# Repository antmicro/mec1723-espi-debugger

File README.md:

# MEC1723 eSPI Debugger

Copyright (c) 2026 [Antmicro](https://www.antmicro.com)

## Overview

This project contains open hardware design files for a debug board based on Microchip MEC1723 embedded controller which includes ARM Cortex-M4 core and eSPI physical interface.
The board is designed to aid development, bring-up and integration of eSPI-based data link between servers (HPMs) and Data Center Secure Control Modules (DC-SCMs).
The board has a 0.1 inch pin header connector which allows to connect it to the eSPI bus in the system under development.
The board provides USB-accessible UART and JTAG interfaces, Port 80 status display and local flash storage for the MEC1723 firmware.
MEC1723 controllers are supported in [Zephyr](https://www.zephyrproject.org/) RTOS

The PCB design files were prepared in KiCad 10.x.

## Key features

* Microchip [MEC1723](https://www.microchip.com/en-us/product/mec1723) embedded controller with ARM Cortex-M4 and eSPI interface
* Generic 0.1 inch pinhead connector
* USB-C port with FTDI FT2232H USB interface bridge
* UART and JTAG interfaces accessible from the USB interface bridge
* 1 Gb QSPI NOR Flash for MEC1723 firmware storage
* Port 80 (POST code) display with dual seven-segment LED indicator
* Tag-Connect headers for debug and programming access
* 62 x 87 mm (2.44 x 3.42 inch) PCB outline

## Project structure

The main directory contains KiCad PCB project files, the LICENSE, and this README, and the img directory contains graphics for this README.

## License

This project is licensed under the [Apache-2.0](LICENSE) license.

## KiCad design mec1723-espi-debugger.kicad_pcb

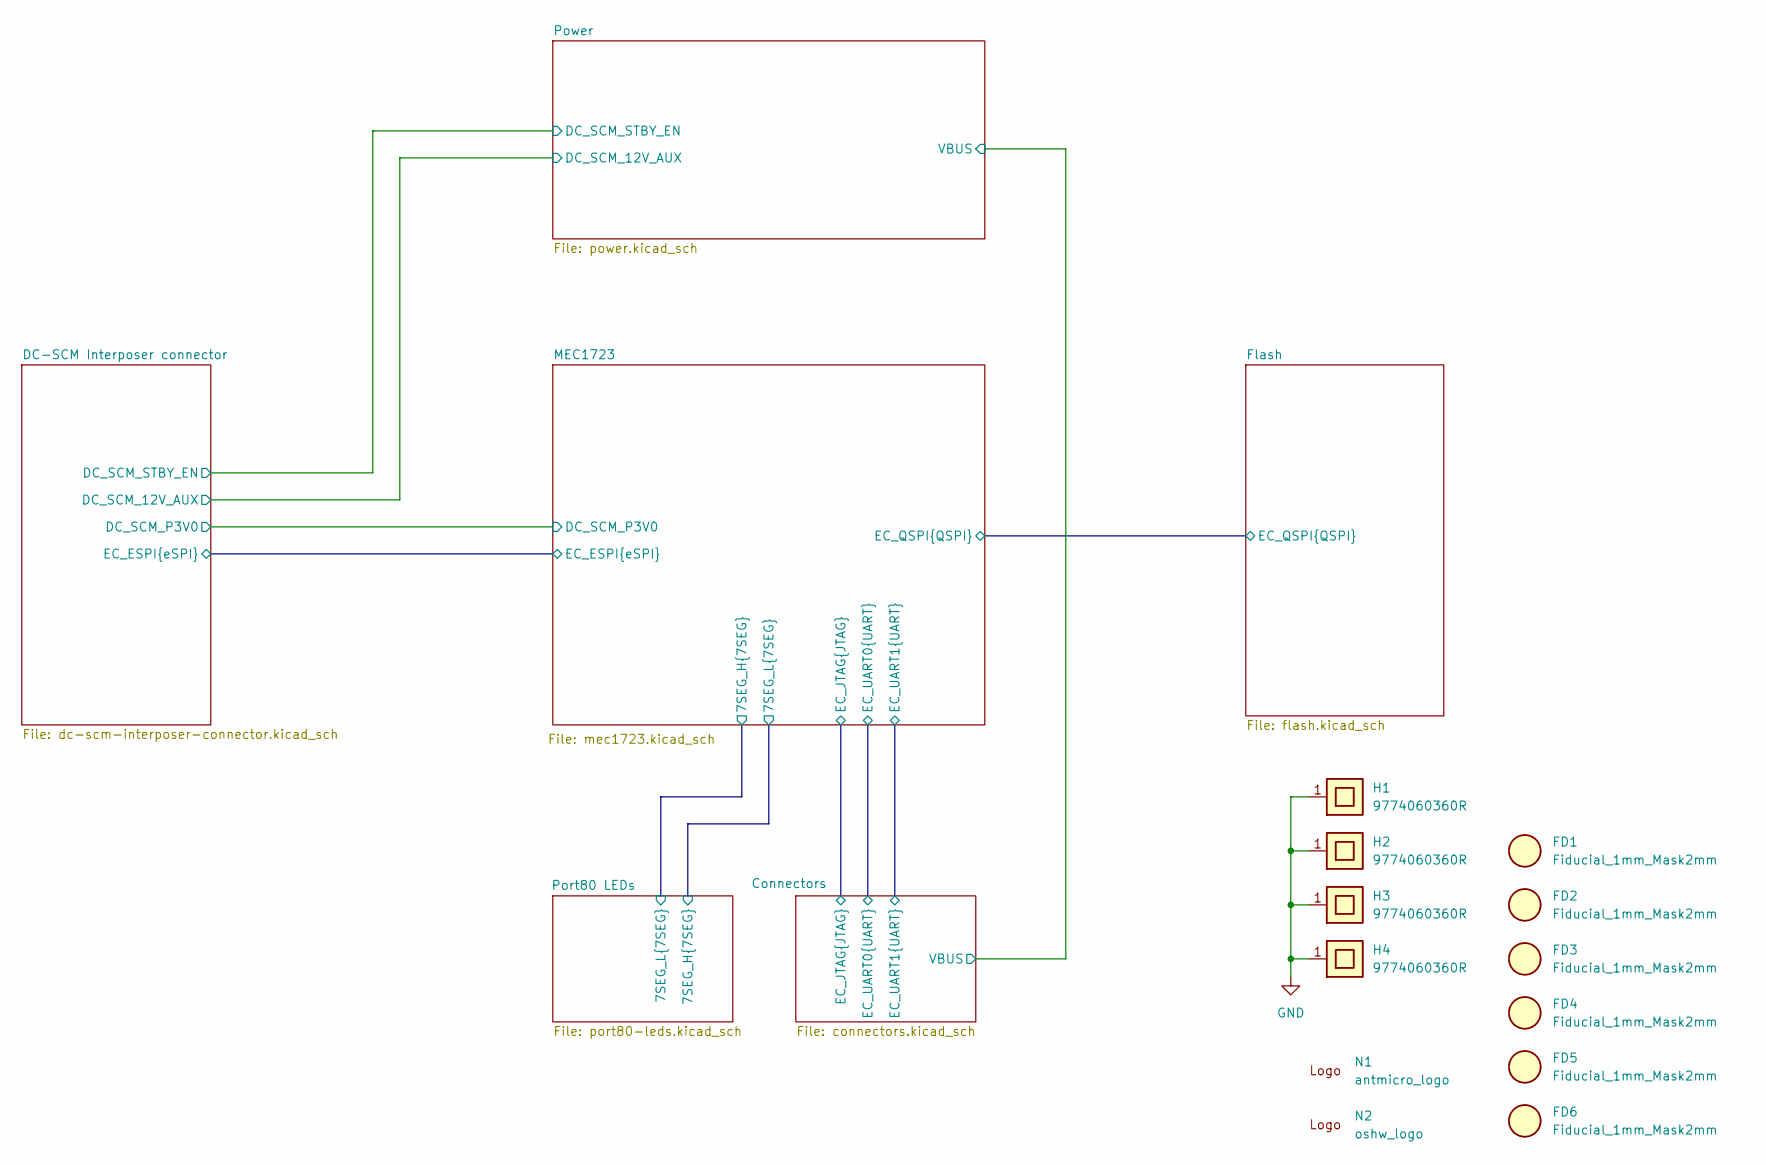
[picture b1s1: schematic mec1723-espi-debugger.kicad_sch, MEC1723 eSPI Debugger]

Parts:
FD1, FD2, FD3, FD4, FD5, FD6: Fiducial_1mm_Mask2mm
H1, H2, H3, H4: Spacer_Drill4.4mm_H6mm_9774060360R; MPN 9774060360R
N1: antmicro_logo; antmicro-logo_scaled_12mm
N2: oshw_logo; oshw-logo

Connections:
GND: H1.1, H2.1, H3.1, H4.1; also elsewhere on the board

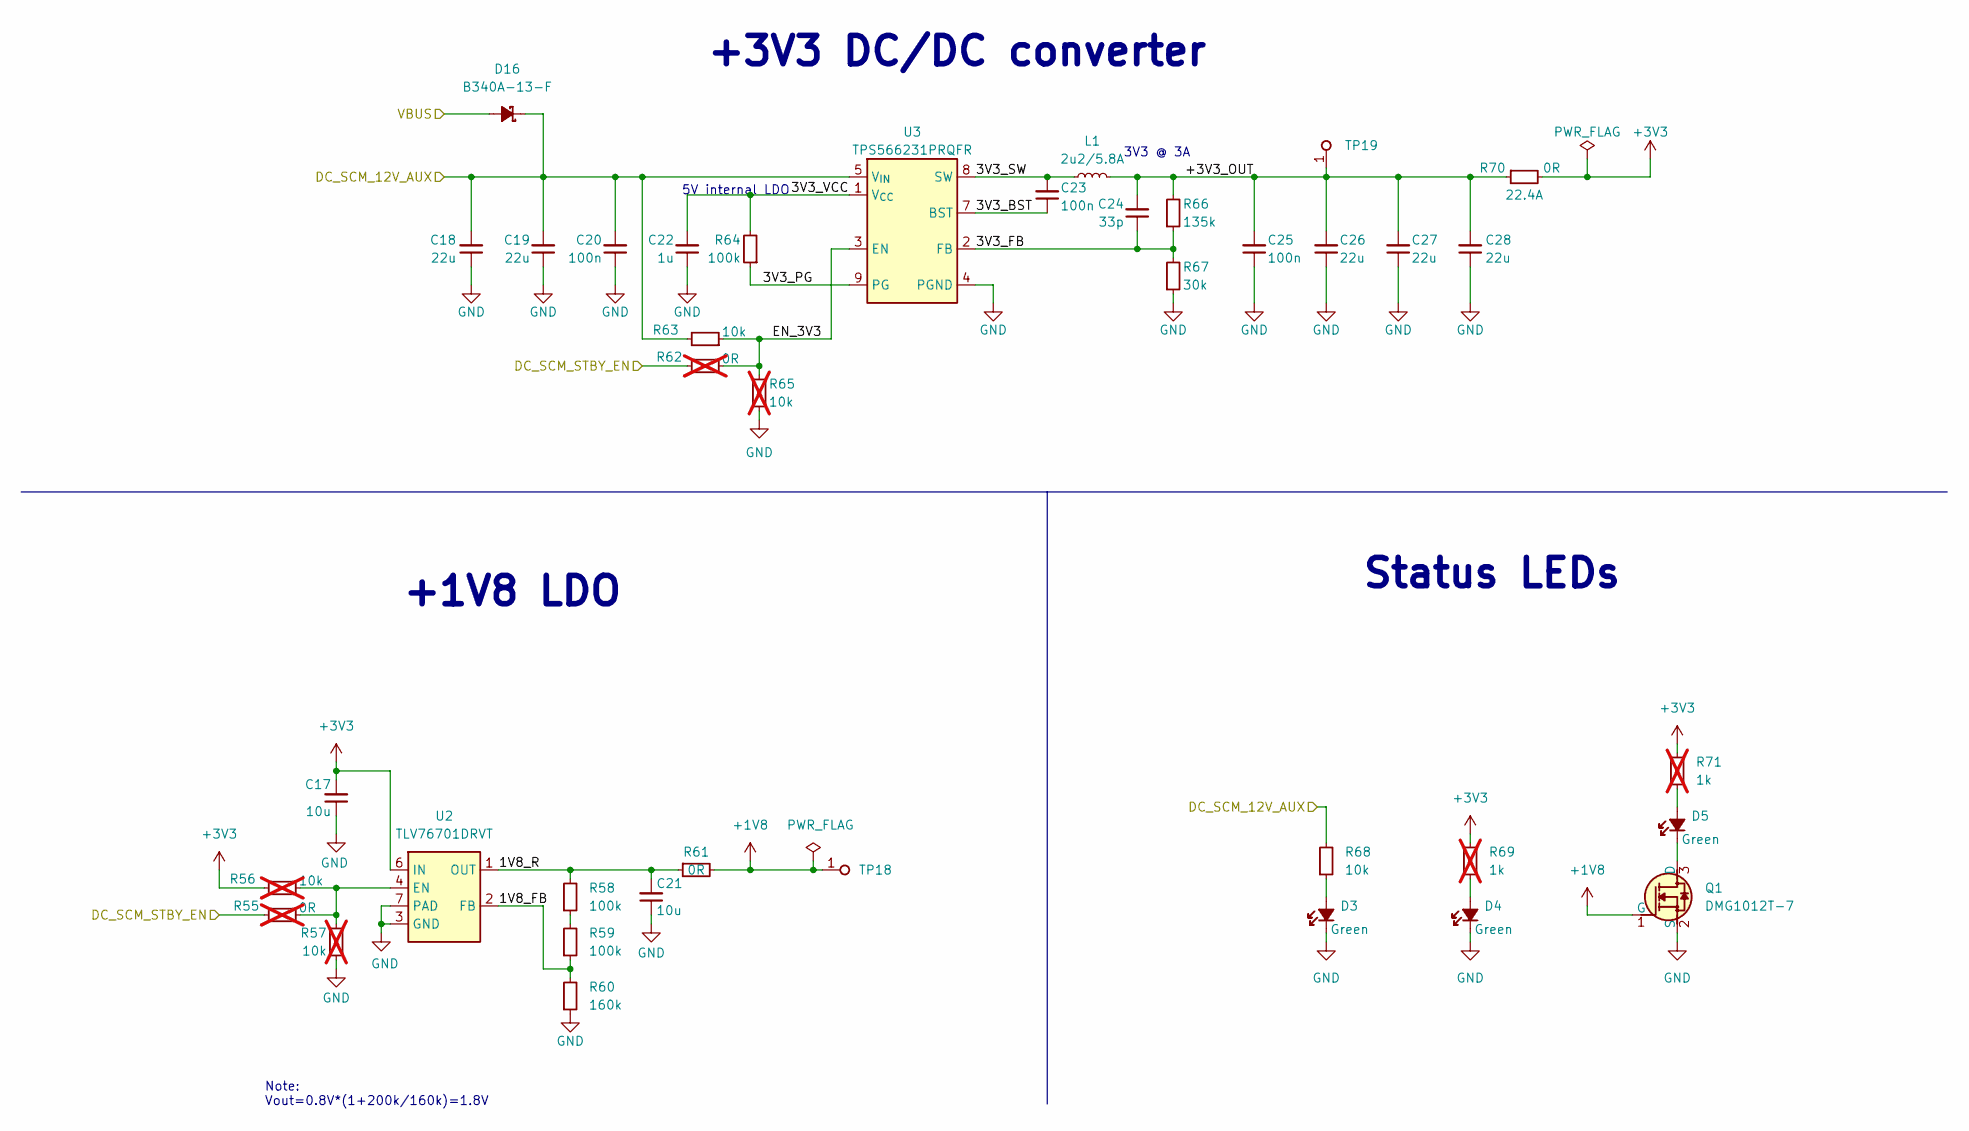
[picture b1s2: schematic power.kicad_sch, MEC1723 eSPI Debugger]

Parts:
C17, C21: C_10u_10V_0402; C_0402_1005Metric; Voltage 10V; MPN GRM155R61A106ME11D
C18, C19, C26, C27, C28: C_22u_16V_0603; C_0603_1608Metric_EIA; Voltage 16V; MPN CL10A226MO7JZNC
C20, C23, C25: C_100n_0402; C_0402_1005Metric; Voltage 50V; MPN GRM155R61H104KE14D
C22: C_1u_25V_0402; C_0402_1005Metric; Voltage 25V; MPN GRM155R61E105KE11J
C24: C_33p_0402; C_0402_1005Metric; MPN 04025A330FAT2A
D3, D4, D5: LED_G_0603_LTST-C190GKT; LED_0603_1608Metric_G; MPN LTST-C190GKT
D16: B340A-13-F; D_SMA; MPN B340A-13-F
L1: L_2u2_5.8A_WE-PMFI-35329222; L_WE-PMFI-353220; MPN 74479335329222
Q1: DMG1012T-7; SOT-523; MPN DMG1012T-7
R55, R62: R_0R_0402; R_0402_1005Metric; MPN ERJ2GE0R00X; not fitted
R56, R57, R65: R_10k_0402; R_0402_1005Metric; Tolerance 1%; MPN CR0402-FX-1002GLF; not fitted
R58, R59, R64: R_100k_0402; R_0402_1005Metric; Tolerance 1%; MPN CR0402-FX-1003GLF
R60: R_160k_0402; R_0402_1005Metric; Tolerance 1%; MPN CR0402-FX-1603GLF
R61: R_0R_0402; R_0402_1005Metric; MPN ERJ2GE0R00X
R63, R68: R_10k_0402; R_0402_1005Metric; Tolerance 1%; MPN CR0402-FX-1002GLF
R66: R_135k_0402; R_0402_1005Metric; Tolerance 0.1%; MPN RT0805BRD07135KL
R67: R_30k_0402; R_0402_1005Metric; Tolerance 1%; MPN CR0402-FX-3002GLF
R69, R71: R_1k_0402; R_0402_1005Metric; Tolerance 1%; MPN CR0402-FX-1001GLF; not fitted
R70: R_0R_22.4A_0603; R_0603_1608Metric; Tolerance template_tolerance; MPN PMR03EZPJ000
TP18, TP19: TP_0.75mm_SMD; TP_SMD_0.75mm
U2: TLV76701_WSON; WSON-6-1EP_2x2mm_P0.65mm; MPN TLV76701DRVT
U3: TPS566231P; VQFN-HR-9_2x1.5mm; MPN TPS566231PRQFR

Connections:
+1V8: Q1.1 (G), R61.2, TP18.1 (1_1); also elsewhere on the board
+3V3: C17.2, R56.2, R69.2, R70.2, R71.2, U2.6 (IN); also elsewhere on the board
/Connectors/VBUS: D16.2 (A); also elsewhere on the board
/DC-SCM Interposer connector/DC_SCM_12V_AUX: C18.2, C19.2, C20.2, D16.1 (C), R63.2, R68.2, U3.5 (V_{IN}), U3.6 (V_{IN}); also elsewhere on the board
/DC-SCM Interposer connector/DC_SCM_STBY_EN: R55.1, R62.1; also elsewhere on the board
/Power/1V8_FB: R59.1, R60.2, U2.2 (FB)
/Power/1V8_R: C21.2, R58.2, R61.1, U2.1 (OUT)
/Power/3V3_BST: C23.1, U3.7 (BST)
/Power/3V3_FB: C24.1, R66.1, R67.2, U3.2 (FB)
/Power/3V3_PG: R64.1, U3.9 (PG)
/Power/3V3_SW: C23.2, L1.1, U3.8 (SW)
/Power/3V3_VCC: C22.2, R64.2, U3.1 (V_{CC})
/Power/+3V3_OUT: C24.2, C25.2, C26.2, C27.2, C28.2, L1.2, R66.2, R70.1, TP19.1 (1_1)
/Power/EN_3V3: R62.2, R63.1, R65.2, U3.3 (EN)
GND: C17.1, C18.1, C19.1, C20.1, C21.1, C22.1, C25.1, C26.1, C27.1, C28.1, D3.1 (C), D4.1 (C), Q1.2 (S), R57.1, R60.1, R65.1, R67.1, U2.3 (GND), U2.5 (GND), U2.7 (PAD), U3.4 (PGND); also elsewhere on the board
unnamed: D3.2 (A), R68.1
unnamed: D4.2 (A), R69.1
unnamed: D5.2 (A), R71.1
unnamed: D5.1 (C), Q1.3 (D)
unnamed: R58.1, R59.2
unnamed: R55.2, R56.1, R57.2, U2.4 (EN)

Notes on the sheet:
Note: Vout=0.8V*(1+200k/160k)=1.8V
Status LEDs
+1V8 LDO
3V3 @ 3A
5V internal LDO
+3V3 DC/DC converter

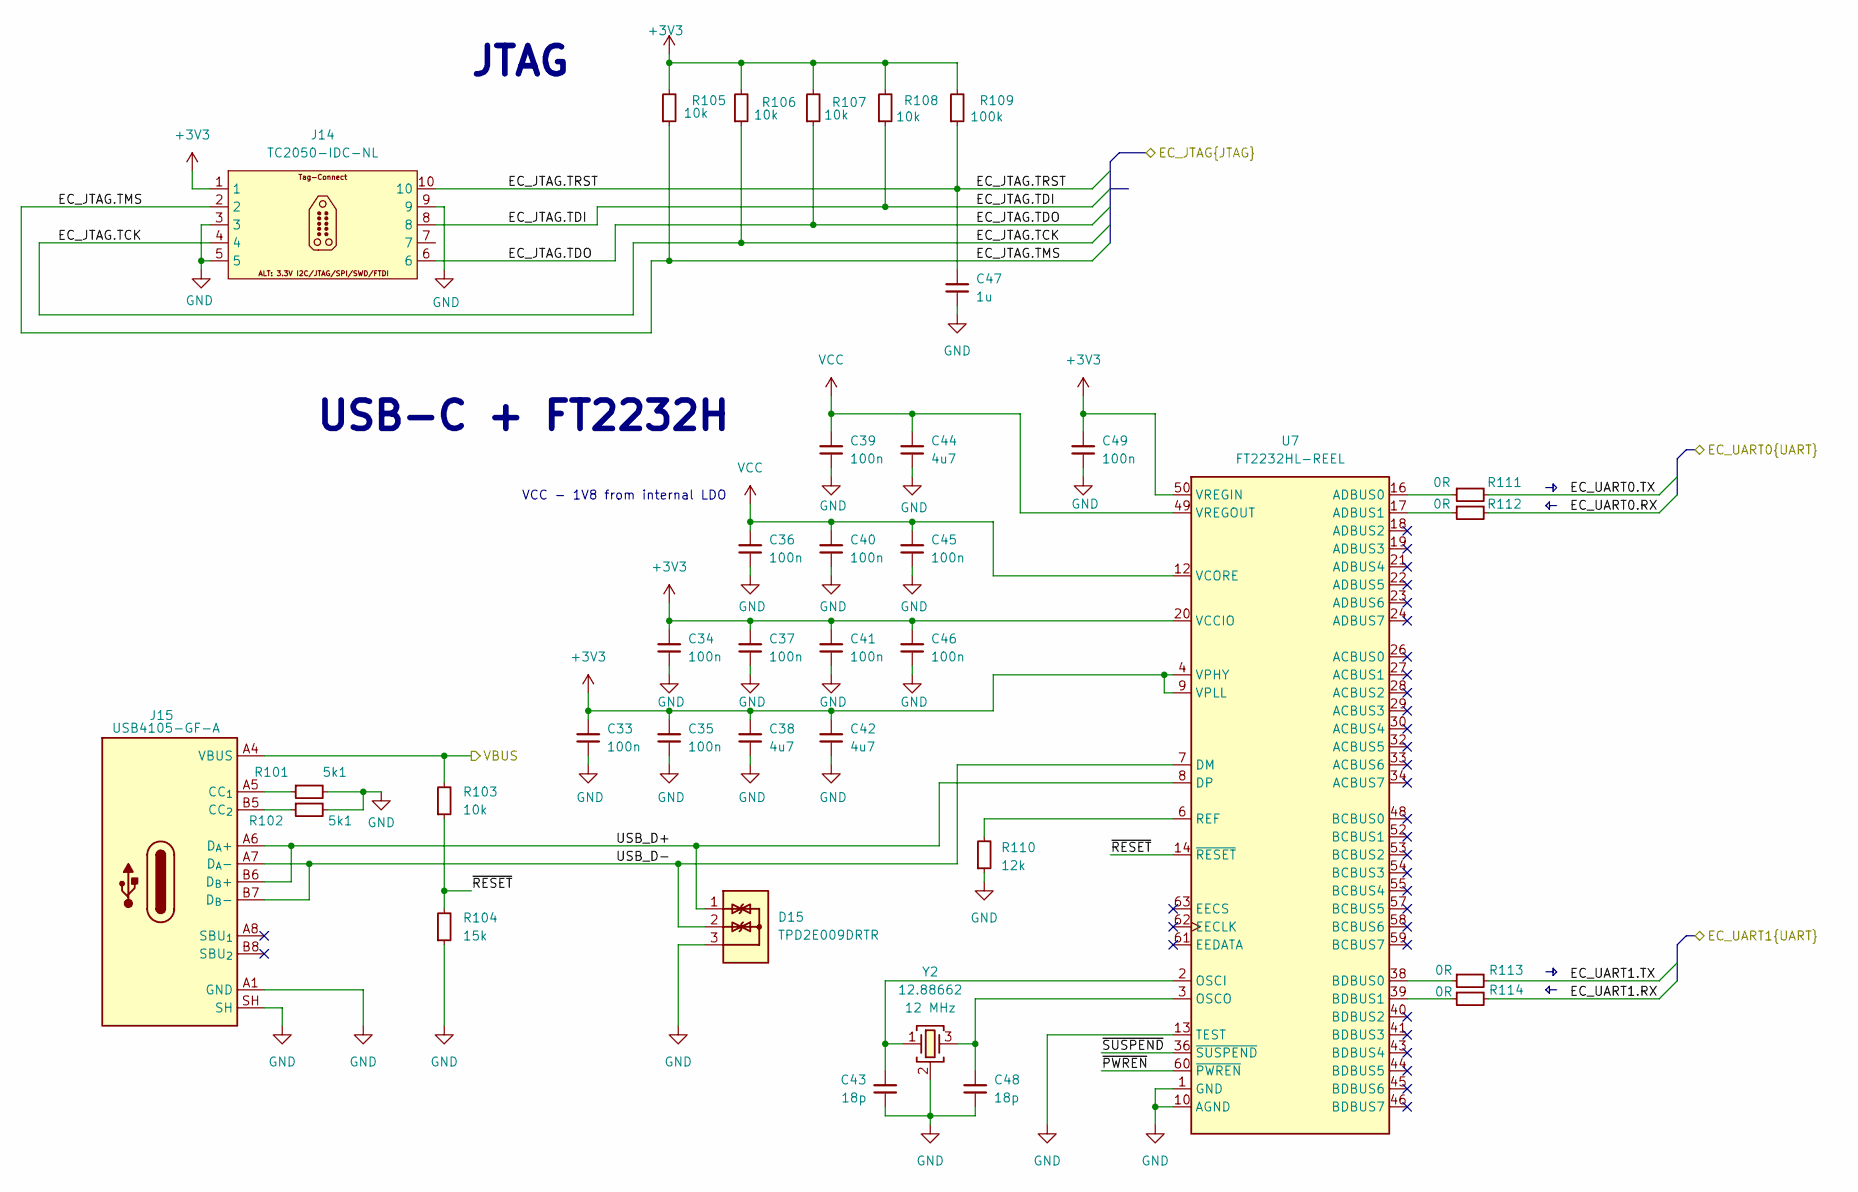
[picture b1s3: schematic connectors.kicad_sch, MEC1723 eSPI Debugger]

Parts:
C33, C34, C35, C36, C37, C39, C40, C41, C45, C46, C49: C_100n_16V_X7R_0402; C_0402_1005Metric; Voltage 16V; MPN C0402C104J4RAC7411
C38, C42, C44: C_4u7_10V_X7T_0402; C_0402_1005Metric; Voltage 10V; MPN GRM155D71A475ME15D
C43, C48: C_18p_0402; C_0402_1005Metric; MPN CL05C180JB51PNC
C47: C_1u_0402; C_0402_1005Metric; MPN C1005X6S1A105K050BC
D15: TPD2E009_SOT-9X3; SOT-723; MPN TPD2E009DRTR
J14: Tag-Connect_TC2050-IDC-NL_2x5_P1.27mm; MPN TC2050-IDC-NL
J15: USB-C_GCT_USB4105-GF-A; USB-C_Receptacle_GCT_USB4105-GF-A; MPN USB4105-GF-A
R101, R102: R_5k1_0402; R_0402_1005Metric; Tolerance 1%; MPN CR0402-FX-5101GLF
R103, R105, R106, R107, R108: R_10k_0402; R_0402_1005Metric; Tolerance 1%; MPN CR0402-FX-1002GLF
R104: R_15k_0402; R_0402_1005Metric; Tolerance 1%; MPN CR0402-FX-1502GLF
R109: R_100k_0402; R_0402_1005Metric; Tolerance 1%; MPN CR0402-FX-1003GLF
R110: R_12k_0402; R_0402_1005Metric; Tolerance 1%; MPN CR0402-FX-1202GLF
R111, R112, R113, R114: R_0R_0402; R_0402_1005Metric; MPN ERJ2GE0R00X
U7: FT2232HL-REEL; LQFP-64_10x10mm_P0.5mm; MPN FT2232HL-REEL
Y2: Resonator_12MHz_KX-7; Resonator_SMD_Geyer_KX-7_3.2x2.5x0.8mm; MPN 12.88662

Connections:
+3V3: C33.2, C34.2, C35.2, C37.2, C38.2, C41.2, C42.2, C46.2, C49.2, J14.1, R105.2, R106.2, R107.2, R108.2, R109.2, U7.4 (VPHY), U7.9 (VPLL), U7.20 (VCCIO), U7.31 (VCCIO), U7.42 (VCCIO), U7.50 (VREGIN), U7.56 (VCCIO); also elsewhere on the board
/Connectors/EC_JTAG.TCK: J14.4, R106.1; also elsewhere on the board
/Connectors/EC_JTAG.TDI: J14.8, R108.1; also elsewhere on the board
/Connectors/EC_JTAG.TDO: J14.6, R107.1; also elsewhere on the board
/Connectors/EC_JTAG.TMS: J14.2, R105.1; also elsewhere on the board
/Connectors/EC_JTAG.TRST: C47.2, J14.10, R109.1; also elsewhere on the board
/Connectors/EC_UART0.RX: R112.2; also elsewhere on the board
/Connectors/EC_UART0.TX: R111.2; also elsewhere on the board
/Connectors/EC_UART1.RX: R114.2; also elsewhere on the board
/Connectors/EC_UART1.TX: R113.2; also elsewhere on the board
/Connectors/USB_D+: D15.1, J15.A6 (D_{A}+), J15.B6 (D_{B}+), U7.8 (DP)
/Connectors/USB_D-: D15.2, J15.A7 (D_{A}-), J15.B7 (D_{B}-), U7.7 (DM)
/Connectors/VBUS: J15.A4 (VBUS), J15.A9 (VBUS), J15.B4 (VBUS), J15.B9 (VBUS), R103.2; also elsewhere on the board
/Connectors/~PWREN: U7.60 (~PWREN)
/Connectors/~RESET: R103.1, R104.2, U7.14 (~RESET)
/Connectors/~SUSPEND: U7.36 (~SUSPEND)
GND: C33.1, C34.1, C35.1, C36.1, C37.1, C38.1, C39.1, C40.1, C41.1, C42.1, C43.1, C44.1, C45.1, C46.1, C47.1, C48.1, C49.1, D15.3, J14.3, J14.5, J14.9, J15.A1 (GND), J15.A12 (GND), J15.B1 (GND), J15.B12 (GND), J15.SH, R101.2, R102.2, R104.1, R110.1, U7.1 (GND), U7.5 (GND), U7.10 (AGND), U7.11 (GND), U7.13 (TEST), U7.15 (GND), U7.25 (GND), U7.35 (GND), U7.47 (GND), U7.51 (GND), Y2.2 (SH), Y2.4 (SH); also elsewhere on the board
unnamed: J15.A5 (CC_{1}), R101.1
unnamed: J15.B5 (CC_{2}), R102.1
unnamed: R111.1, U7.16 (ADBUS0)
unnamed: R112.1, U7.17 (ADBUS1)
unnamed: R113.1, U7.38 (BDBUS0)
unnamed: R114.1, U7.39 (BDBUS1)
unnamed: C43.2, U7.2 (OSCI), Y2.1
unnamed: C48.2, U7.3 (OSCO), Y2.3
unnamed: R110.2, U7.6 (REF)
VCC: C36.2, C39.2, C40.2, C44.2, C45.2, U7.12 (VCORE), U7.37 (VCORE), U7.49 (VREGOUT), U7.64 (VCORE)

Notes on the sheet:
VCC - 1V8 from internal LDO
JTAG
USB-C + FT2232H

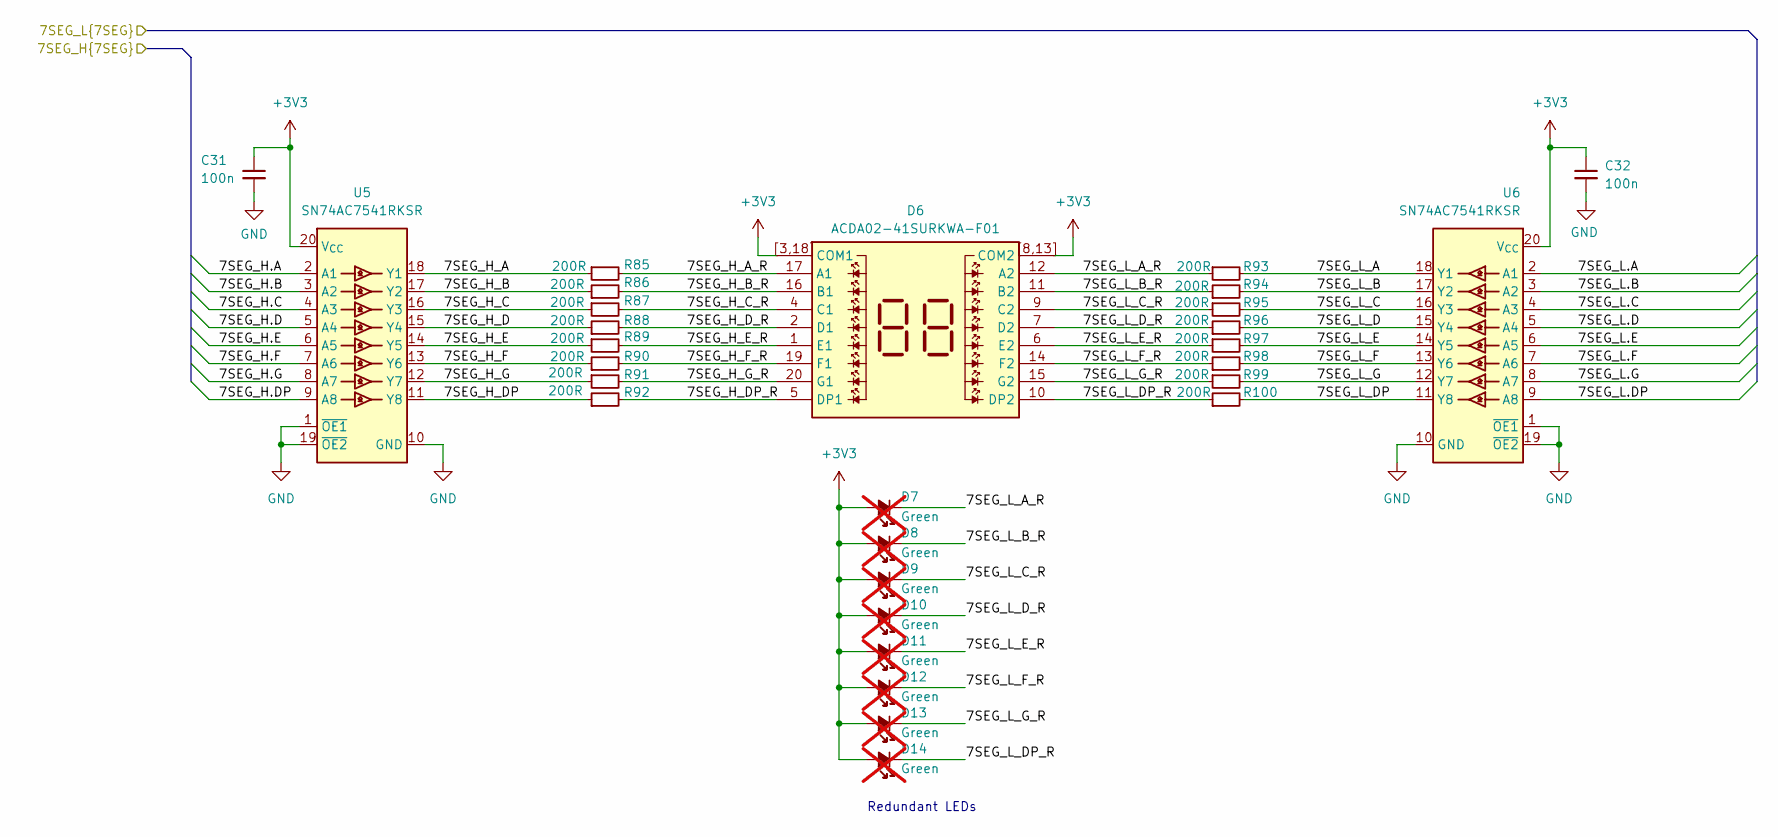
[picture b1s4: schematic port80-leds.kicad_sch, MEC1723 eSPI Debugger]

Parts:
C31, C32: C_100n_0402; C_0402_1005Metric; Voltage 50V; MPN GRM155R61H104KE14D
D6: ACDA02-41SURKWA-F01; MPN ACDA02-41SURKWA-F01
D7, D8, D9, D10, D11, D12, D13, D14: LED_G_0603_LTST-C190GKT; LED_0603_1608Metric_G; MPN LTST-C190GKT; not fitted
R85, R86, R87, R88, R89, R90, R91, R92, R93, R94, R95, R96, R97, R98, R99, R100: R_200R_0402; R_0402_1005Metric; Tolerance 1%; MPN CR0402-FX-2000GLF
U5, U6: SN74AC7541_VQFN; VQFN-20_1EP_4.5x2.5mm_P0.5mm; MPN SN74AC7541RKSR

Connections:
+3V3: C31.1, C32.1, D6.3 (COM1), D6.8 (COM2), D6.13 (COM2), D6.18 (COM1), D6.[3,18] (COM1), D6.[8,13] (COM2), D7.2 (A), D8.2 (A), D9.2 (A), D10.2 (A), D11.2 (A), D12.2 (A), D13.2 (A), D14.2 (A), U5.20 (V_{CC}), U6.20 (V_{CC}); also elsewhere on the board
/MEC1723/7SEG_H.A: U6.2 (A1); also elsewhere on the board
/MEC1723/7SEG_H.B: U6.3 (A2); also elsewhere on the board
/MEC1723/7SEG_H.C: U6.4 (A3); also elsewhere on the board
/MEC1723/7SEG_H.D: U6.5 (A4); also elsewhere on the board
/MEC1723/7SEG_H.DP: U6.9 (A8); also elsewhere on the board
/MEC1723/7SEG_H.E: U6.6 (A5); also elsewhere on the board
/MEC1723/7SEG_H.F: U6.7 (A6); also elsewhere on the board
/MEC1723/7SEG_H.G: U6.8 (A7); also elsewhere on the board
/MEC1723/7SEG_L.A: U5.2 (A1); also elsewhere on the board
/MEC1723/7SEG_L.B: U5.3 (A2); also elsewhere on the board
/MEC1723/7SEG_L.C: U5.4 (A3); also elsewhere on the board
/MEC1723/7SEG_L.D: U5.5 (A4); also elsewhere on the board
/MEC1723/7SEG_L.DP: U5.9 (A8); also elsewhere on the board
/MEC1723/7SEG_L.E: U5.6 (A5); also elsewhere on the board
/MEC1723/7SEG_L.F: U5.7 (A6); also elsewhere on the board
/MEC1723/7SEG_L.G: U5.8 (A7); also elsewhere on the board
/Port80 LEDs/7SEG_H_A: R85.1, U5.18 (Y1)
/Port80 LEDs/7SEG_H_A_R: D6.17 (A1), R85.2
/Port80 LEDs/7SEG_H_B: R86.1, U5.17 (Y2)
/Port80 LEDs/7SEG_H_B_R: D6.16 (B1), R86.2
/Port80 LEDs/7SEG_H_C: R87.1, U5.16 (Y3)
/Port80 LEDs/7SEG_H_C_R: D6.4 (C1), R87.2
/Port80 LEDs/7SEG_H_D: R88.1, U5.15 (Y4)
/Port80 LEDs/7SEG_H_DP: R92.1, U5.11 (Y8)
/Port80 LEDs/7SEG_H_DP_R: D6.5 (DP1), R92.2
/Port80 LEDs/7SEG_H_D_R: D6.2 (D1), R88.2
/Port80 LEDs/7SEG_H_E: R89.1, U5.14 (Y5)
/Port80 LEDs/7SEG_H_E_R: D6.1 (E1), R89.2
/Port80 LEDs/7SEG_H_F: R90.1, U5.13 (Y6)
/Port80 LEDs/7SEG_H_F_R: D6.19 (F1), R90.2
/Port80 LEDs/7SEG_H_G: R91.1, U5.12 (Y7)
/Port80 LEDs/7SEG_H_G_R: D6.20 (G1), R91.2
/Port80 LEDs/7SEG_L_A: R93.2, U6.18 (Y1)
/Port80 LEDs/7SEG_L_A_R: D6.12 (A2), D7.1 (C), R93.1
/Port80 LEDs/7SEG_L_B: R94.2, U6.17 (Y2)
/Port80 LEDs/7SEG_L_B_R: D6.11 (B2), D8.1 (C), R94.1
/Port80 LEDs/7SEG_L_C: R95.2, U6.16 (Y3)
/Port80 LEDs/7SEG_L_C_R: D6.9 (C2), D9.1 (C), R95.1
/Port80 LEDs/7SEG_L_D: R96.2, U6.15 (Y4)
/Port80 LEDs/7SEG_L_DP: R100.2, U6.11 (Y8)
/Port80 LEDs/7SEG_L_DP_R: D6.10 (DP2), D14.1 (C), R100.1
/Port80 LEDs/7SEG_L_D_R: D6.7 (D2), D10.1 (C), R96.1
/Port80 LEDs/7SEG_L_E: R97.2, U6.14 (Y5)
/Port80 LEDs/7SEG_L_E_R: D6.6 (E2), D11.1 (C), R97.1
/Port80 LEDs/7SEG_L_F: R98.2, U6.13 (Y6)
/Port80 LEDs/7SEG_L_F_R: D6.14 (F2), D12.1 (C), R98.1
/Port80 LEDs/7SEG_L_G: R99.2, U6.12 (Y7)
/Port80 LEDs/7SEG_L_G_R: D6.15 (G2), D13.1 (C), R99.1
GND: C31.2, C32.2, U5.1 (~OE1), U5.10 (GND), U5.19 (~OE2), U5.21 (GND), U6.1 (~OE1), U6.10 (GND), U6.19 (~OE2), U6.21 (GND); also elsewhere on the board

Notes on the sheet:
Redundant LEDs

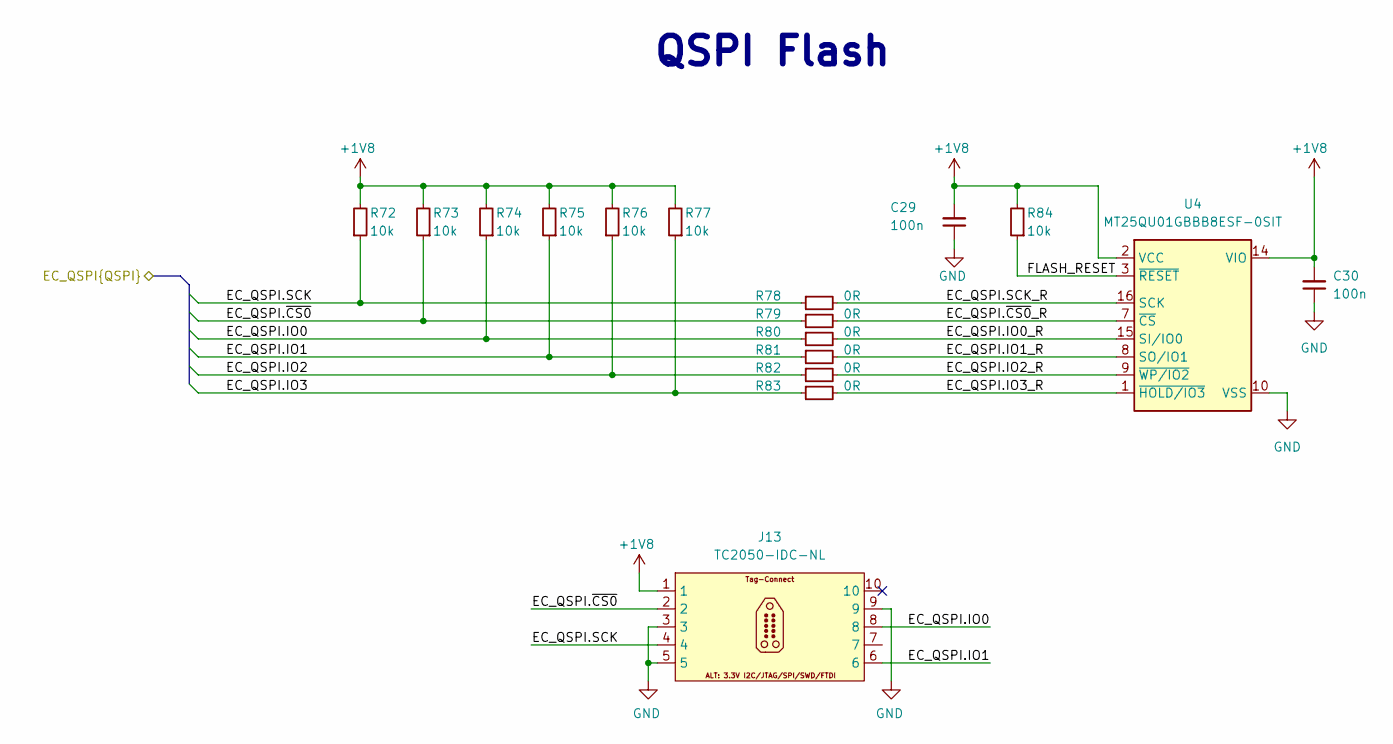
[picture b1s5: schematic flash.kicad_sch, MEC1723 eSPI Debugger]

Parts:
C29, C30: C_100n_0402; C_0402_1005Metric; Voltage 50V; MPN GRM155R61H104KE14D
J13: Tag-Connect_TC2050-IDC-NL_2x5_P1.27mm; MPN TC2050-IDC-NL
R72, R73, R74, R75, R76, R77, R84: R_10k_0402; R_0402_1005Metric; Tolerance 1%; MPN CR0402-FX-1002GLF
R78, R79, R80, R81, R82, R83: R_0R_0402; R_0402_1005Metric; MPN ERJ2GE0R00X
U4: MT25QU01GBBB8_SOIC; SOIC-16_W7.5mm; MPN MT25QU01GBBB8ESF-0SIT

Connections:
+1V8: C29.2, C30.2, J13.1, R72.2, R73.2, R74.2, R75.2, R76.2, R77.2, R84.2, U4.2 (VCC), U4.14 (VIO); also elsewhere on the board
/Flash/EC_QSPI.IO0: J13.8, R74.1, R80.1; also elsewhere on the board
/Flash/EC_QSPI.IO0_R: R80.2, U4.15 (SI/IO0)
/Flash/EC_QSPI.IO1: J13.6, R75.1, R81.1; also elsewhere on the board
/Flash/EC_QSPI.IO1_R: R81.2, U4.8 (SO/IO1)
/Flash/EC_QSPI.IO2: R76.1, R82.1; also elsewhere on the board
/Flash/EC_QSPI.IO2_R: R82.2, U4.9 (~WP/IO2)
/Flash/EC_QSPI.IO3: R77.1, R83.1; also elsewhere on the board
/Flash/EC_QSPI.IO3_R: R83.2, U4.1 (~HOLD/IO3)
/Flash/EC_QSPI.SCK: J13.4, R72.1, R78.1; also elsewhere on the board
/Flash/EC_QSPI.SCK_R: R78.2, U4.16 (SCK)
/Flash/EC_QSPI.~CS0: J13.2, R73.1, R79.1; also elsewhere on the board
/Flash/EC_QSPI.~CS0_R: R79.2, U4.7 (~CS)
/Flash/FLASH_RESET: R84.1, U4.3 (~RESET)
GND: C29.1, C30.1, J13.3, J13.5, J13.9, U4.10 (VSS); also elsewhere on the board

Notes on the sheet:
QSPI Flash

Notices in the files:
parts and their libraries:
License: Apache-2.0
